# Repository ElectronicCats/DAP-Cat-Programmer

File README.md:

# CMSIS-DAP Cat Programmer

<a href="https://github.com/ElectronicCats/DAP-Cat-Programmer/wiki">
  
</a>

<p align=center>

</p>

## Description
An Open-Source CMSIS-DAP Debug Probe based on DAPLink. DAP Cat Programmer is a low-cost $5.00 USD debug probe based on the CMSIS-DAP (also known as DAPLink) protocol standard and USB-Serial conversion, and it can realize USB conversion to serial interface. It can be used to program and debug the application software running on Arm Cortex Microcontrollers.

The probe comes with indicator LEDs, a button to reset the target or trigger the firmware update, a reversible USB-C connector, and an easy-to-use 10-pin 2.54mm Header.

## Special Thanks

- [Deqing Sun](https://github.com/DeqingSun)
- CH552 Group in Telegram

## How to contribute 
 Contributions are welcome! 

Please read the document  [**Contribution Manual**](https://github.com/ElectronicCats/electroniccats-cla/blob/main/electroniccats-contribution-manual.md)  which will show you how to contribute your changes to the project.

✨ Thanks to all our [contributors](https://github.com/ElectronicCats/Cat-Sink/graphs/contributors)! ✨

See [**_Electronic Cats CLA_**](https://github.com/ElectronicCats/electroniccats-cla/blob/main/electroniccats-cla.md) for more information.

See the  [**community code of conduct**](https://github.com/ElectronicCats/electroniccats-cla/blob/main/electroniccats-community-code-of-conduct.md) for a vision of the community we want to build and what we expect from it."			

## License
LGPL

Electronic Cats invests time and resources providing this open source design, please support Electronic Cats and open-source hardware by purchasing products from Electronic Cats!

Designed by Electronic Cats.

Firmware released under an GNU LGPL v3.0 license. See the LICENSE file for more information.

Hardware released under an CERN Open Hardware Licence v1.2. See the LICENSE_HARDWARE file for more information.

Electronic Cats is a registered trademark, please do not use if you sell these PCBs.

29 Agu 2020

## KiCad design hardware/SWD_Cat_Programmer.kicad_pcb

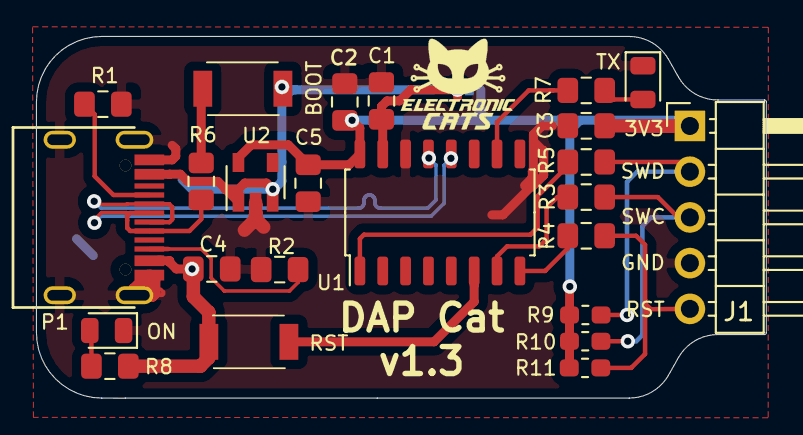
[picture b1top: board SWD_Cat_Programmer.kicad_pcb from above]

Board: 2 copper layers, 40.5 x 20.1 mm, 25 parts (1 on the bottom side), 19 nets.

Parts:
BOOT: BOOT; TS1088R02026
C1, C2, C3: 0.1uF; C_0805_2012Metric_Pad1.15x1.40mm_HandSolder
C4, C5: 1uF; C_0805_2012Metric_Pad1.15x1.40mm_HandSolder
J1: DEBUG_OUTPUT; PinHeader_1x05_P2.54mm_Horizontal
JP1: Jumper; SolderJumper-3_P1.3mm_Bridged12_RoundedPad1.0x1.5mm
ON: LED; LED_0805_2012Metric
P1: USB_C_Plug_USB2.0; C393939
R1, R2: 5.1K; R_0805_2012Metric_Pad1.15x1.40mm_HandSolder
R3, R4, R5: 150; R_0805_2012Metric_Pad1.15x1.40mm_HandSolder
R6: 20K; R_0805_2012Metric_Pad1.15x1.40mm_HandSolder
R7, R8: 1K; R_0805_2012Metric_Pad1.15x1.40mm_HandSolder
R9, R10, R11: 70; R_0603_1608Metric_Pad1.05x0.95mm_HandSolder
RST: RST; TS1088R02026
TX: LED; LED_0805_2012Metric
U1: CH552G; SOP-16_4.55x10.3mm_P1.27mm
U2: AP2112K-3.3; SOT-23-5

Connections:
+3V3: C2.1, C3.1, C5.1, J1.1, JP1.1, R9.2, R10.2, R11.2, U1.16, U2.5
+5V: BOOT.1, C4.1, JP1.3, P1.A4, R8.2, RST.1, U2.1, U2.3
/D+: P1.A6, R6.1, U1.12
/D-: P1.A7, U1.13
/LED: R7.2, U1.10
/RESET: J1.5, R4.1, R11.1
/RST: RST.2, U1.6
/SWCLK: J1.3, R3.1, R10.1
/SWDIO: J1.2, R5.1, R9.1
GND: C1.2, C2.2, C3.2, C4.2, C5.2, J1.4, ON.1, P1.A1, P1.S1, R1.1, R2.1, TX.1, U1.14, U2.2
unnamed: C1.1, JP1.2, U1.15
unnamed: R7.1, TX.2
unnamed: ON.2, R8.1
unnamed: P1.A5, R1.2
unnamed: P1.B5, R2.2
unnamed: R3.2, U1.7
unnamed: R4.2, U1.8
unnamed: R5.2, U1.1
unnamed: BOOT.2, R6.2

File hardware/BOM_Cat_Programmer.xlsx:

SWD_CAT_PROGRAMMER |  |  |  |  | USD | USD
Descripción | Referencia | Número de Parte | Proveedor | Cantidad | Precio | Total 10 Unidades
USB C Connector | P1 | C393939 | LCSC | 1 | 0.11738999999999999 | 1.1738999999999999
100 nF Capacitor | C1, C2, C3 | C49678 | LCSC | 3 | 8.2489999999999994E-3 | 0.24746999999999997
5.1k Resistor | R1,R2 | C105874 | LCSC | 2 | 2.274E-3 | 4.548E-2
MCU 8-Bit FLASH E8051 32MHz | U1 | C111292 | LCSC | 1 | 0.42 | 4.2
1K Resistor | R7 | C25623 | LCSC | 1 | 1.835E-3 | 1.8350000000000002E-2
LED | D1 | C131244 | LCSC | 2 | 1.9605999999999998E-2 | 0.39211999999999997
PUSH Switch | SW1, SW2 | 612-TL3342F160 | Mouser | 2 | 0.82 | 16.399999999999999
20K Resistor | R6 | C702832 | LCSC | 1 | 1.8140000000000001E-3 | 1.814E-2
150 Resistor | R3,R4,R5 | C103997 | LCSC | 3 | 2.8400000000000001E-3 | 8.5199999999999998E-2
1uF Capacitor | C4,C5 | C28323 | LCSC | 2 | 1.5793999999999999E-2 | 0.31587999999999999
Regulator | U2 | C296123 | LCSC | 1 | 2.6419000000000002E-2 | 0.26419000000000004
 |  |  |  | Total | 1.436221 | 23.160729999999997

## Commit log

2020-08-02 Init Schematic
2020-08-04 Bom and footprints added
2020-08-05 capacitors modified
2020-08-06 added logos EC
2020-08-06 labels added
2020-08-06 modifed design
2020-08-06 buttons changed
2020-08-07 Pull up Resistors Update
2020-08-07 jumper voltage
2020-08-08 Jumper
2020-08-09 update label
2020-08-29 Create LICENSE
2020-08-29 Create LICENSE_HARDWARE
2020-08-30 change path hardware
2020-08-30 Added firmware for Electronic Cats hardware
2020-09-01 pin output changed
2020-09-01 fix path for Arduino
2020-09-02 v1.1 align
2020-09-03 update some data
2020-09-23 Docs
2020-09-23 example photo
2020-09-23 Added example USBSerial Adaptor
2020-09-23 Add link wiki
2020-09-23 Add Drivers Windows
2020-09-27 Update labels for Serial Adapter
2020-10-13 abierto open hardware month edition
2020-11-06 Cupper Zones Fixed
2020-11-06 enhanced routing
2020-11-06 Fix labels, added contribution name Ricardo Mena
2020-12-14 Fix USB and DAP for PyOCD and Keil
2020-12-15 fix multiple command issue
2021-05-26 add guide hacksterio
2021-05-27 add image for wiki
2021-05-27 add cfg scripts for openOCD
2021-05-27 add screenshot for wiki
2021-05-27 add wiki screenshot
2022-08-23 Updated Readme.md
    wiki and getting started link added
2022-09-29 Issue template added
2023-01-07 Revert "enhanced routing"
    This reverts commit 42d6ad708d969779b1270b3bd74ecf01ee581fea.
2023-11-14 Update README.md
    Price updated.
    Zadig photo updated.
2023-12-20 Update README.md
    Changes:
    1.- Adding pictures of the device to the general information section and wiki section.
    2.- Adding a button and the link to the store
    3.- Adding a button and the link to the wiki
    4.- Removing information about technical features, drivers and manuals to the wiki
2023-12-21 Update README.md
    Changes in the button to the store
2023-12-22 Update README.md
    Updates on device pictures (no version visible)
2023-12-26 Update README.md
    Rearrange of the pictures with the links to the store and wiki.
2024-04-11 feat(docs):Update README.md
    Add how to contribute
2024-08-12 fix:Update README.md
    To update device's cost and resize the main picture
2024-08-12 fix:Update README.md
    To resize the device's picture
